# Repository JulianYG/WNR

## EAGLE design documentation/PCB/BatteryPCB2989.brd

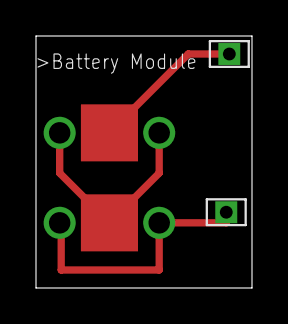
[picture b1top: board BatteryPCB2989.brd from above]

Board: 2 copper layers, 12.0 x 14.0 mm, 4 parts (0 on the bottom side), 3 nets.

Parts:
GND: FTS-101-03-L-S; SAMTEC_FTS-101-03-S
U$1, U$2: 2989NOHOLE
VDD: FTS-101-03-L-S; SAMTEC_FTS-101-03-S

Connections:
unnamed: U$1.NEG, U$2.P0S2, U$2.POS1
unnamed: GND.1, U$2.NEG
unnamed: U$1.P0S2, U$1.POS1, VDD.1
